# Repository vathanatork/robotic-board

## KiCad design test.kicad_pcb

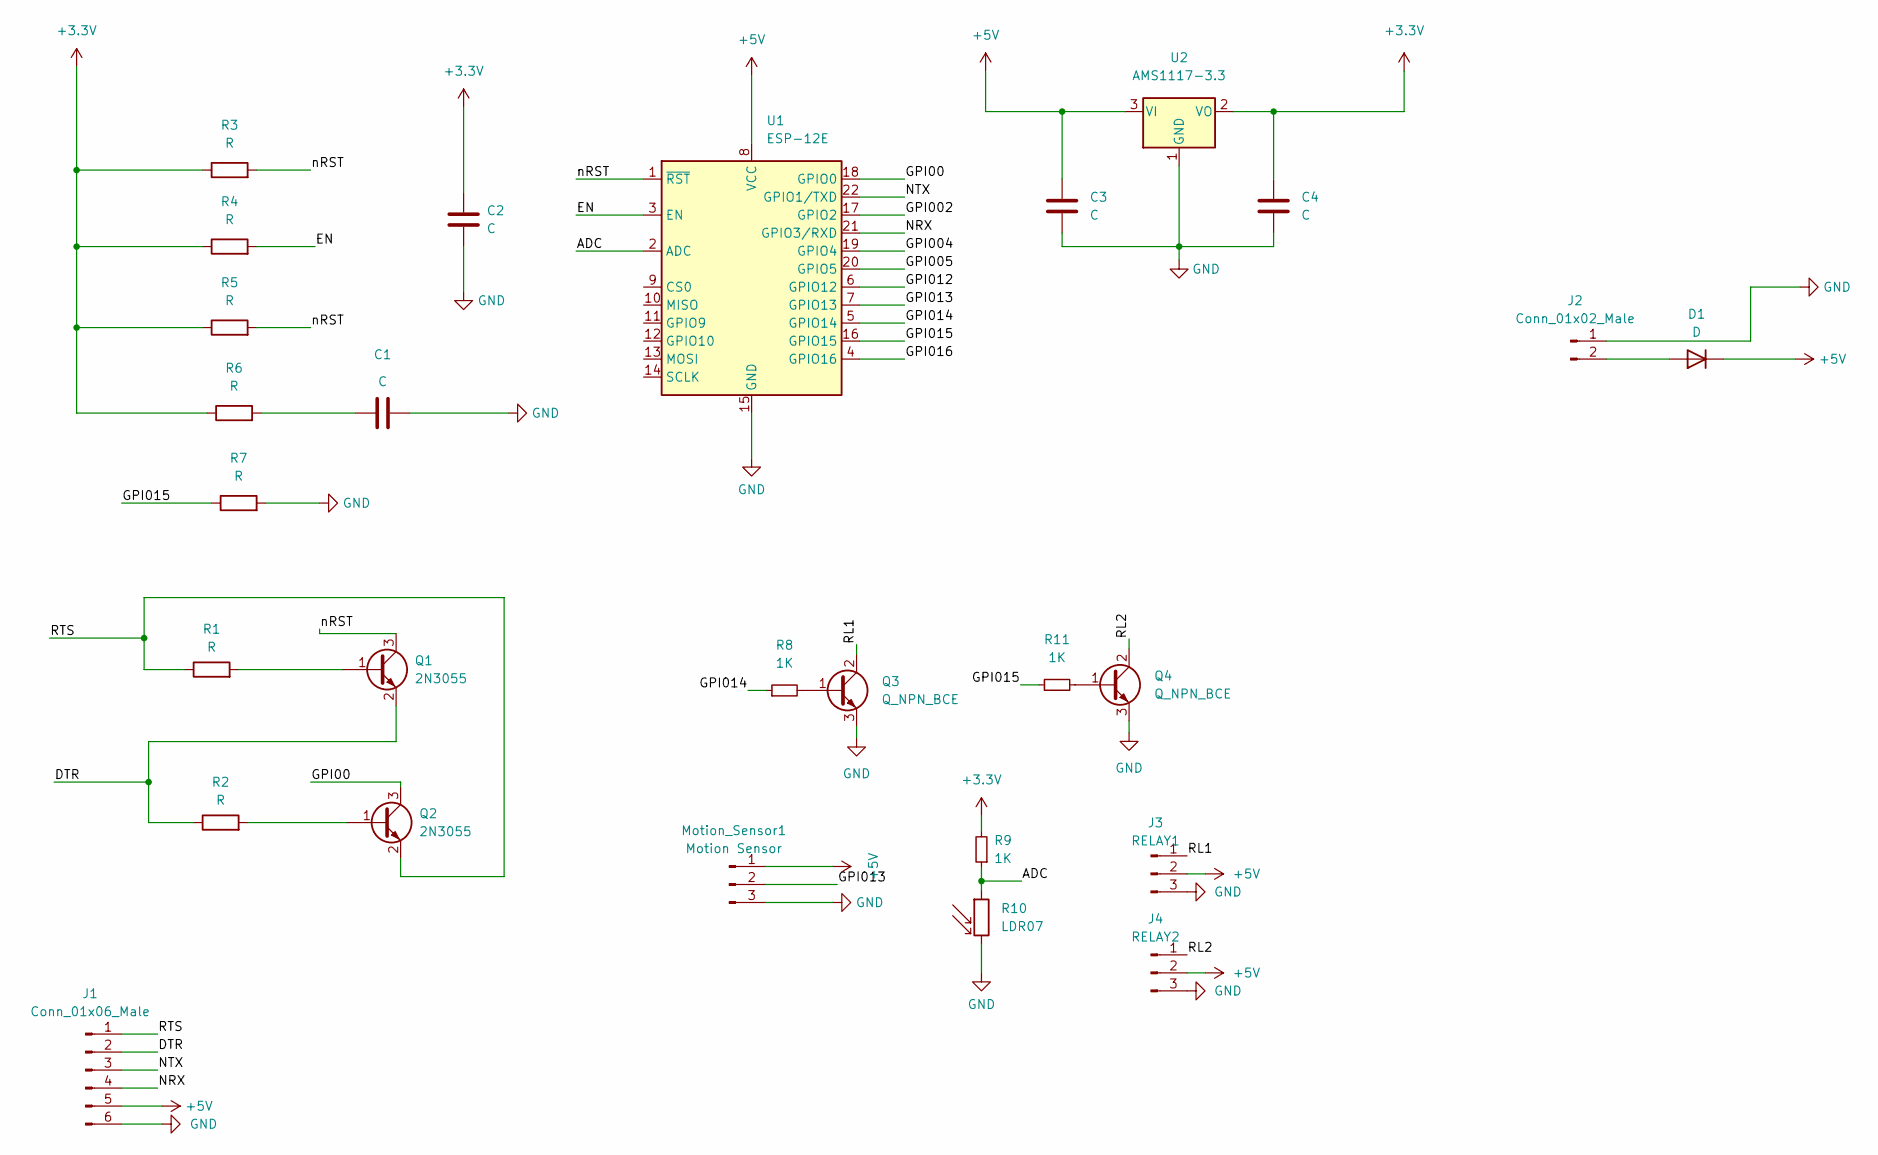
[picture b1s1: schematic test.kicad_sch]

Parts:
C1, C3, C4: C; C_0603_1608Metric
C2: C; CP_Elec_3x5.4
D1: D; D_1206_3216Metric
J1: Conn_01x06_Male; JST_EH_B6B-EH-A_1x06_P2.50mm_Vertical
J2: Conn_01x02_Male; JST_EH_B2B-EH-A_1x02_P2.50mm_Vertical
J3: RELAY1; PinSocket_1x03_P2.54mm_Vertical
J4: RELAY2; PinSocket_1x03_P2.54mm_Vertical
Motion_Sensor1: Motion Sensor; PinSocket_1x03_P2.54mm_Vertical
Q1, Q2: 2N3055; SOT-23
Q3, Q4: Q_NPN_BCE; SOT-23
R1, R2, R3: R; R_0201_0603Metric
R4, R5, R6, R7: R; R_0201_0603Metric_Pad0.64x0.40mm_HandSolder
R8, R9, R11: 1K; R_0201_0603Metric
R10: LDR07; R_LDR_5.1x4.3mm_P3.4mm_Vertical
U1: ESP-12E
U2: AMS1117-3.3; SOT-223-3_TabPin2

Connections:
+5V: C3.1, D1.1 (K), J1.5, J3.2, J4.2, Motion_Sensor1.1, U1.8 (VCC), U2.3 (VI)
/ADC: R9.1, R10.1, U1.2 (ADC)
/DTR: J1.2, Q1.2 (E), R2.1
/EN: R4.2, U1.3 (EN)
/GPI00: Q2.3 (C), U1.18 (GPIO0)
/GPI002: U1.17 (GPIO2)
/GPI004: U1.19 (GPIO4)
/GPI005: U1.20 (GPIO5)
/GPI012: U1.6 (GPIO12)
/GPI013: Motion_Sensor1.2, U1.7 (GPIO13)
/GPI014: R8.1, U1.5 (GPIO14)
/GPI015: R7.1, R11.1, U1.16 (GPIO15)
/GPI016: U1.4 (GPIO16)
/NRX: J1.4, U1.21 (GPIO3/RXD)
/NTX: J1.3, U1.22 (GPIO1/TXD)
/RL1: J3.1, Q3.2 (C)
/RL2: J4.1, Q4.2 (C)
/RTS: J1.1, Q2.2 (E), R1.1
/nRST: Q1.3 (C), R3.2, R5.2, U1.1 (~RST)
GND: C1.2, C2.1, C3.2, C4.2, J1.6, J2.1, J3.3, J4.3, Motion_Sensor1.3, Q3.3 (E), Q4.3 (E), R7.2, R10.2, U1.15 (GND), U2.1 (GND)
unnamed: C1.1, R6.2
unnamed: D1.2 (A), J2.2
unnamed: Q1.1 (B), R1.2
unnamed: Q2.1 (B), R2.2
unnamed: Q3.1 (B), R8.2
unnamed: Q4.1 (B), R11.2

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
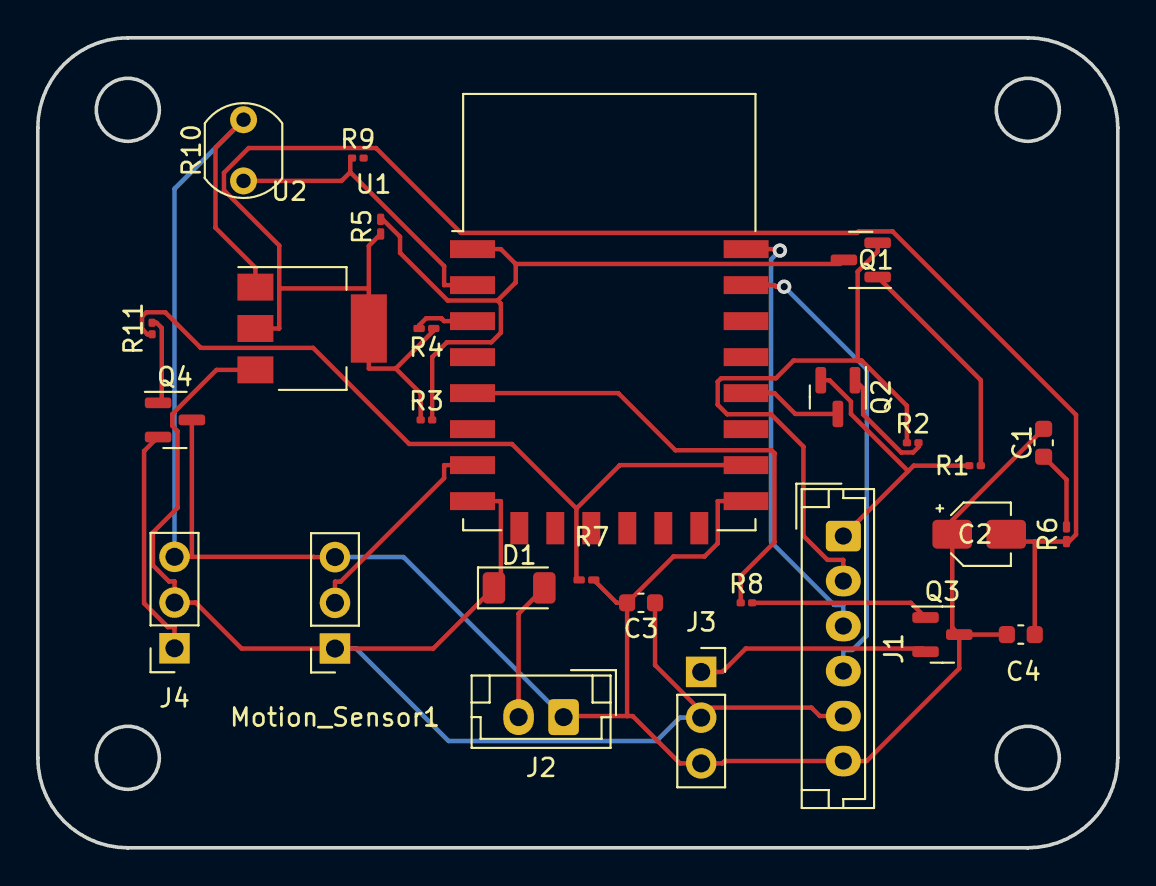
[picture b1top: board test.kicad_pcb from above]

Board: 2 copper layers, 60.0 x 45.0 mm, 27 parts (0 on the bottom side), 22 nets.

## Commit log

2022-12-06 commit roboic project board file
